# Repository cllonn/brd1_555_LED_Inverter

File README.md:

# 555 Timer Board Project
Sara's first PCB design board and is used for testing and measuring signals.

## Project Overview
Used 555 timer, Hex inverter and multiple LEDs to demostrate best design principles, current flow, and real-world testing using the testpoints. The circuit operates by pluging in the USB-C which gives us 5V to generate the 1kHz, 50% duty cycle signla using the 555timer, which then drives LEDs through different resistances. Additionally, a 3.3V LDO powers the hex inverted used for signal inversion and LED control.

## Features
- 555 Timer Circuit: Generates a 1 kHz square wave with 50% duty cycle.
- LED Driver: The 555 output drives four red LEDs through different resistances (10kΩ, 1kΩ, 300Ω, and 50Ω), demonstrating current variation.
- Voltage Regulation: A 3.3V LDO provides power to additional circuit components.
- Hex Inverter: - Outputs a testable logic high and logic low signal.
                - Inverts the 555 timer output and sends it to a test point.
                - Drives three additional LEDs via 50Ω resistors, using the 555 timer signal.

## Circuit Schematic

## PCB Layout

## Usage
To use the board:
1. Insert the USB-C Cabel
2. LED 1,2,3,4 should be oscillating at diffferent brighness
3. (if the LEDs dont blink) check voltage from the OUT pin and it should be oscillating
4. Use testpoints and verify the labels
5. Verify that the hex inverter LEDs doesnt blink with the 555 timer LEDs since they have to be opposite

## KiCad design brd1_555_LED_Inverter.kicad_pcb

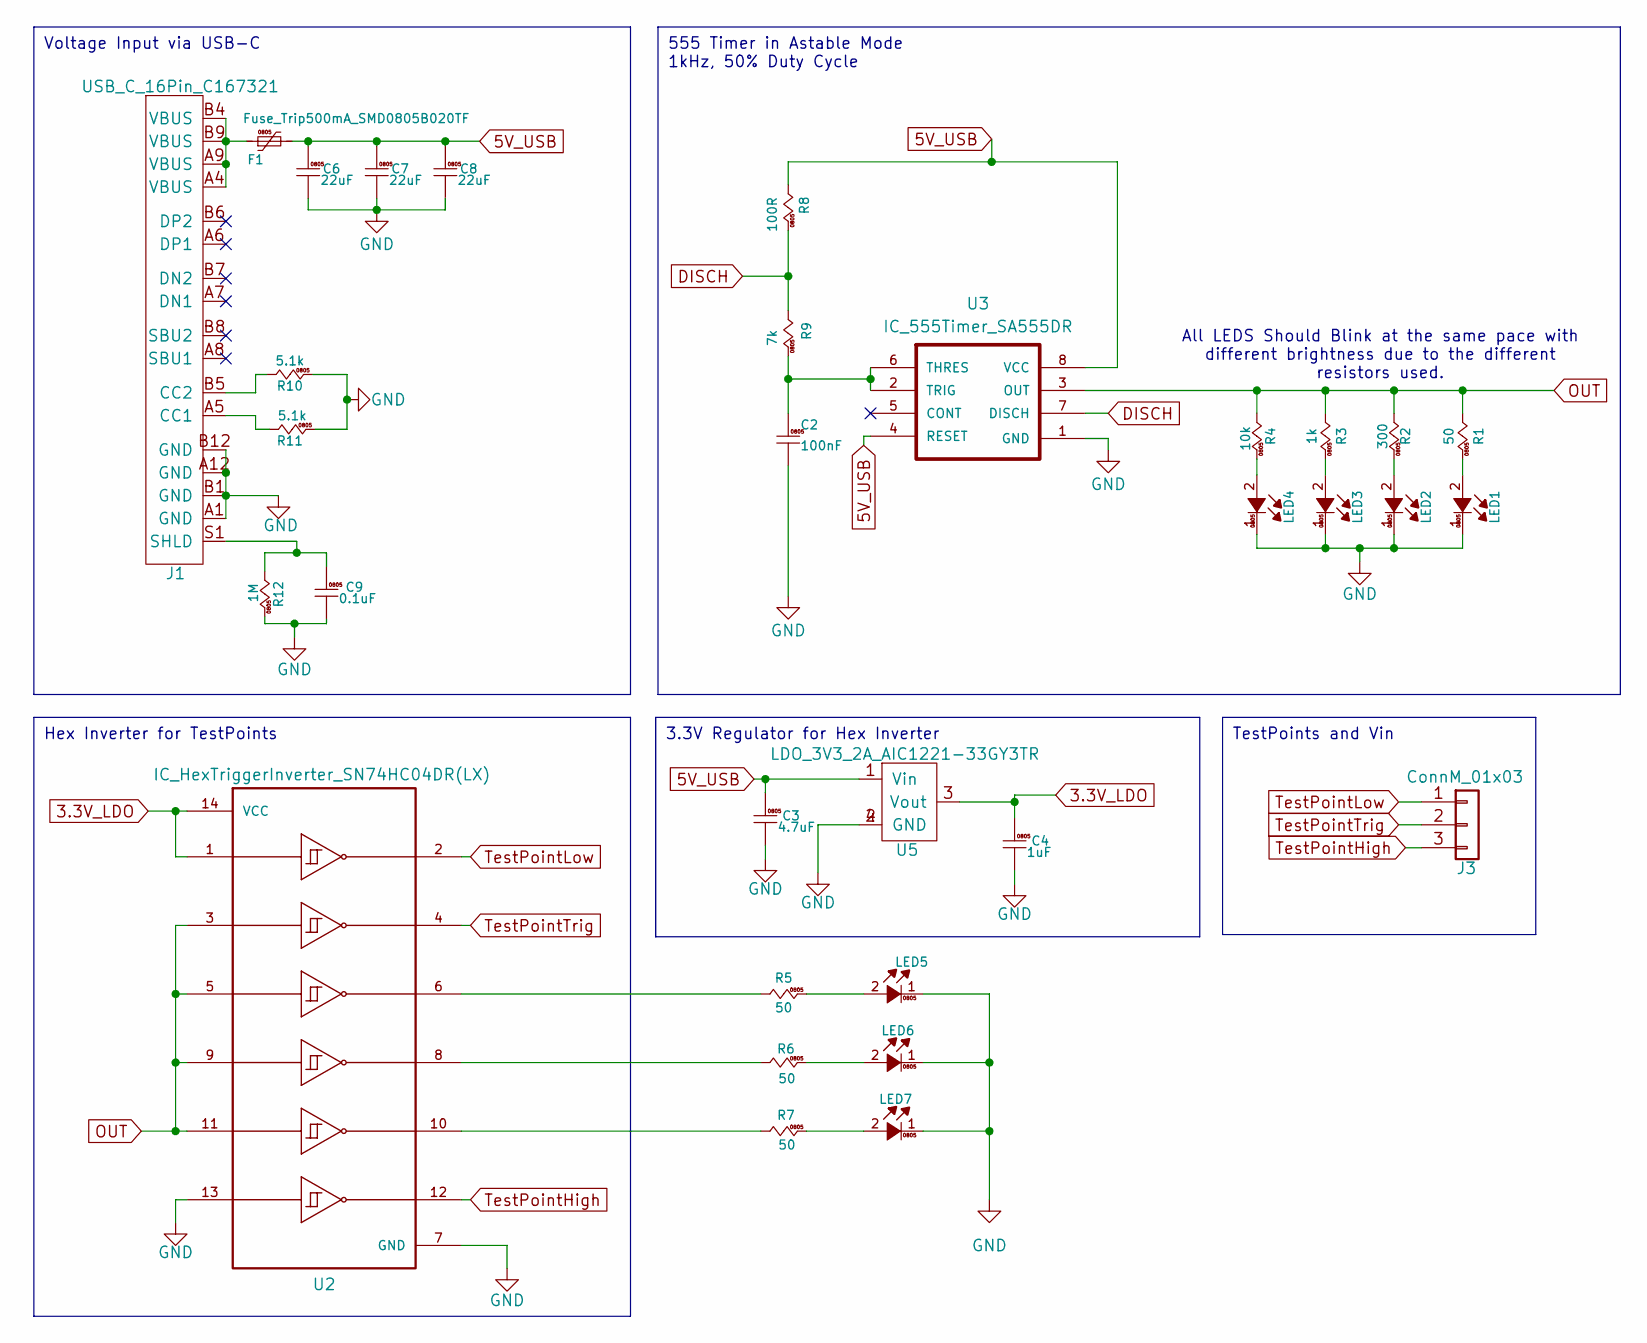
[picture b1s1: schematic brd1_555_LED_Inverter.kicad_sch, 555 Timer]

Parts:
C2: 100nF; C_0805_2012m
C3: 4.7uF; C_0805_2012m
C4: 1uF; C_0805_2012m
C6, C7, C8: 22uF; C_0805_2012m
C9: 0.1uF; C_0805_2012m
F1: Fuse_Trip500mA_SMD0805B020TF; Fuse_0805_2012m
J1: USB_C_16Pin_C167321
J3: ConnM_01x03; PinHeader_1x03_P2.54mm_Vertical
LED1, LED2, LED3, LED4, LED5, LED6, LED7: LED_0805_2012m_Red
R1, R5, R6, R7: 50; R_0805_2012m
R2: 300; R_0805_2012m
R3: 1k; R_0805_2012m
R4: 10k; R_0805_2012m
R8: 100R; R_0805_2012m
R9: 7k; R_0805_2012m
R10, R11: 5.1k; R_0805_2012m
R12: 1M; R_0805_2012m
U2: IC_HexTriggerInverter_SN74HC04DR(LX); SOIC-14_3.9x8.7mm_P1.27mm
U3: IC_555Timer_SA555DR; SOIC-8_3.9x4.9mm_P1.27mm
U5: LDO_3V3_2A_AIC1221-33GY3TR; SOT-223

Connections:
3.3V_LDO: C4.1, U2.1, U2.14 (VCC), U5.3 (Vout)
5V_USB: C3.1, C6.1, C7.1, C8.1, F1.2, R8.1, U3.4 (RESET), U3.8 (VCC), U5.1 (Vin)
DISCH: R8.2, R9.1, U3.7 (DISCH)
GND: C2.2, C3.2, C4.2, C6.2, C7.2, C8.2, C9.2, J1.A1 (GND), J1.A12 (GND), J1.B1 (GND), J1.B12 (GND), LED1.1, LED2.1, LED3.1, LED4.1, LED5.1, LED6.1, LED7.1, R10.2, R11.2, R12.2, U2.7 (GND), U2.13, U3.1 (GND), U5.2 (GND), U5.4 (GND)
unnamed: F1.1, J1.A4 (VBUS), J1.A9 (VBUS), J1.B4 (VBUS), J1.B9 (VBUS)
unnamed: J1.A5 (CC1), R11.1
unnamed: J1.B5 (CC2), R10.1
unnamed: C9.1, J1.S1 (SHLD), R12.1
unnamed: LED1.2, R1.2
unnamed: LED2.2, R2.2
unnamed: LED3.2, R3.2
unnamed: LED4.2, R4.2
unnamed: LED5.2, R5.2
unnamed: LED6.2, R6.2
unnamed: LED7.2, R7.2
unnamed: R5.1, U2.6
unnamed: R6.1, U2.8
unnamed: R7.1, U2.10
unnamed: C2.1, R9.2, U3.2 (TRIG), U3.6 (THRES)
OUT: R1.1, R2.1, R3.1, R4.1, U2.3, U2.5, U2.9, U2.11, U3.3 (OUT)
TestPointHigh: J3.3, U2.12
TestPointLow: J3.1, U2.2
TestPointTrig: J3.2, U2.4

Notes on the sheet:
Hex Inverter for TestPoints
555 Timer in Astable Mode 1kHz, 50% Duty Cycle
3.3V Regulator for Hex Inverter
TestPoints and Vin
Voltage Input via USB-C
All LEDS Should Blink at the same pace with different brightness due to the different resistors used.

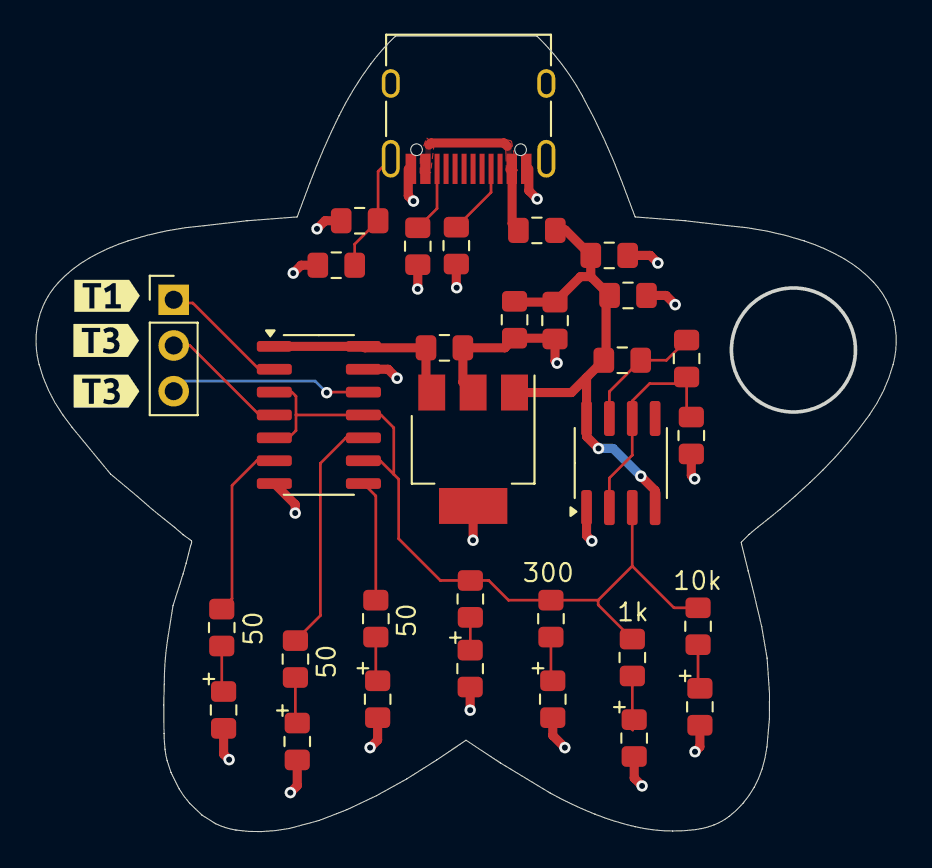
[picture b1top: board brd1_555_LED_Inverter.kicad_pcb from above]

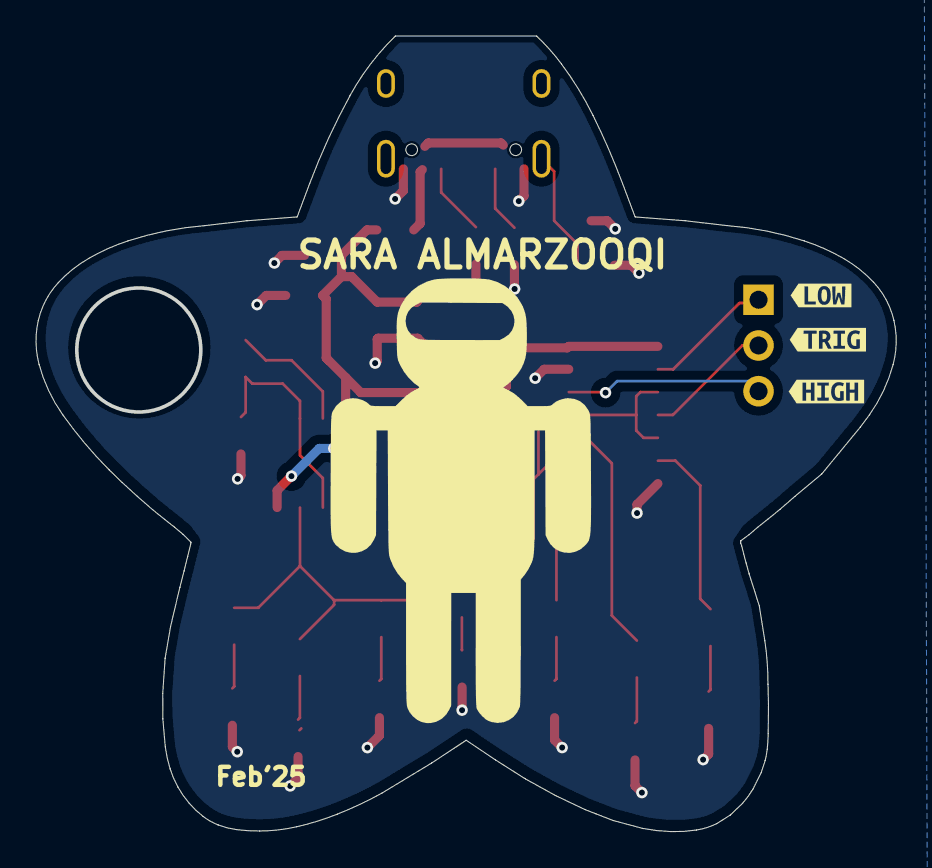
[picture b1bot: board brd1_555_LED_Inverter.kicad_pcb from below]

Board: 2 copper layers, 47.6 x 44.0 mm, 38 parts (3 on the bottom side), 23 nets.

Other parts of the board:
kibuzzard-67A70D0F: G***; kibuzzard-67A70D0F
kibuzzard-67A70DD7: G***; kibuzzard-67A70DD7
kibuzzard-67A70DE1: G***; kibuzzard-67A70DE1
kibuzzard-67A70F8E: G***; kibuzzard-67A70F8E
kibuzzard-67A70FA5: G***; kibuzzard-67A70FA5
kibuzzard-67A70FB4: G***; kibuzzard-67A70FB4

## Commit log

2025-02-08 Initial commit: Added KiCad project files
2025-02-13 Updated Version
2025-02-15 Last Update - Changed width of power trace
2025-02-15 Minor changes
2025-02-16 Updated README file
2025-02-18 Added name on layout / Added Schem+Layout images and updated README / Added Gerber output files
